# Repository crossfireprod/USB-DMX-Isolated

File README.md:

Fully Isolated USB DMX Adapter
==================

This USB DMX adapter is designed to be an functional foray into PCB design and assembly using primarily surface mount components.  The use of an isolating RS-485 transceiver differentiates this USB DMX adapter from others that can be purchased or built at a similar price point.

Bill Of Materials
-------------------

A Bill Of Materials detailing the specific parts used in my most recent production run can be found on [Octopart](https://octopart.com/bom-tool/TxEq1b9y).  Pricing is more or less optimized around single unit quanties.

Repository Contents
-------------------

* **/Hardware** - Eagle Schematic & PCB Layout
* **/Images** - Images of the schematic / PCB design, as well as fully assembled USB DMX adapters.

License
-------------------

All contents of this repository are released under [Creative Commons Share-alike 4.0](http://creativecommons.org/licenses/by-sa/4.0/).

NOTE:  While every effort was made to follow the necessary design rules to maintain proper isolation between the USB and RS-485 interfaces, this design is a hobby project and as such should *not* be relied upon to protect life, limb, your equipment, etc.

Design By: [*ZachCross.com*](https://ZachCross.com)

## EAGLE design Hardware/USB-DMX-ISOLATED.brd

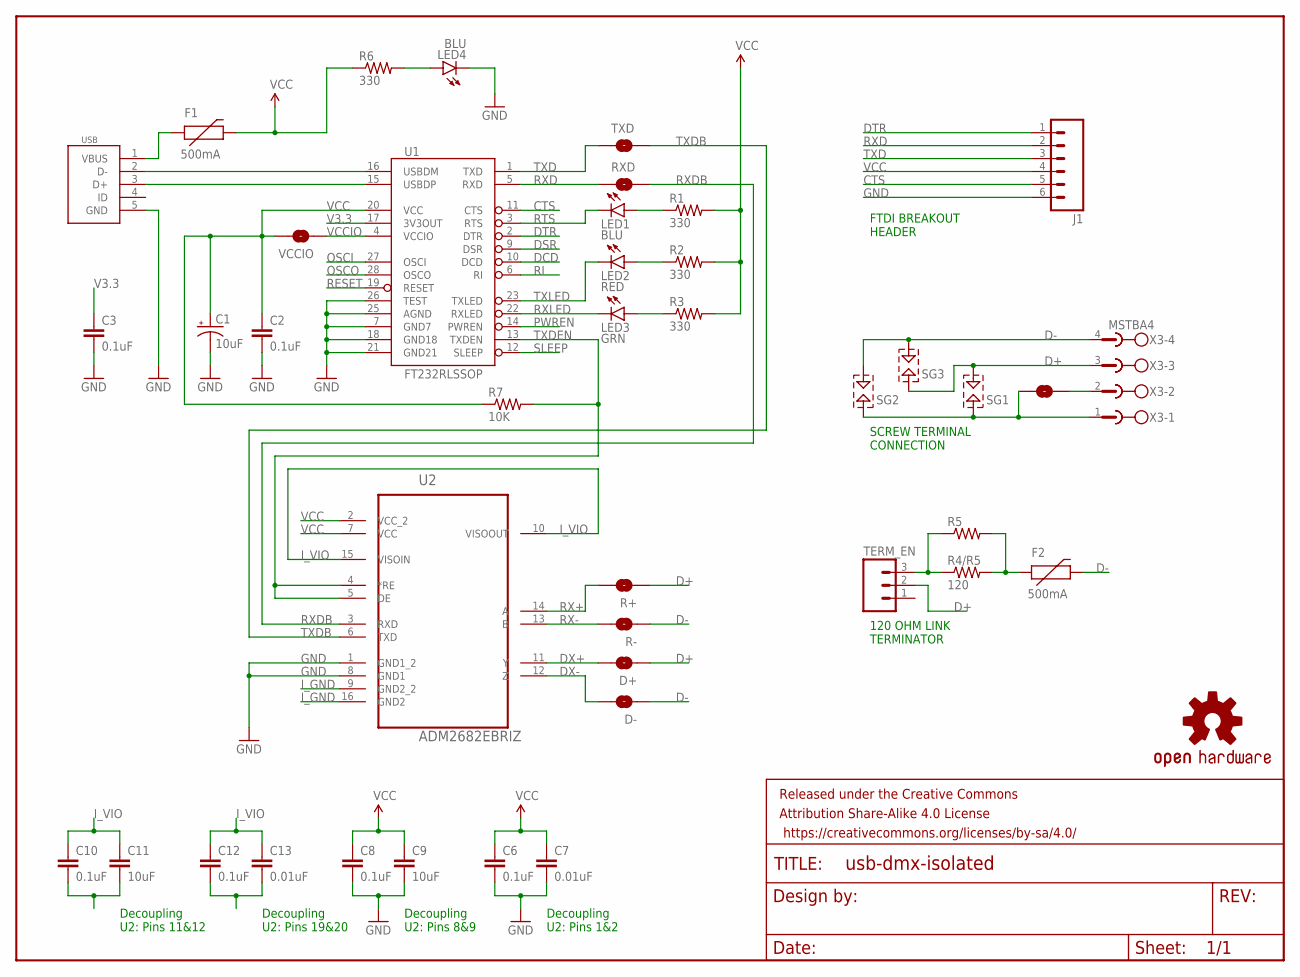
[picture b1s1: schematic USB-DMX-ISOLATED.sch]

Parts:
C1: 10uF; EIA3216
C2, C3, C6, C8, C10, C12: 0.1uF; 1206
C7, C13: 0.01uF; 1206
C9, C11: 10uF; 1206
D+: SOLDERJUMPERTRACE; SJ_2S-TRACE
D-: SOLDERJUMPERTRACE; SJ_2S-TRACE
F1, F2: 500mA; PTC-1206
FRAME1: FRAME-LETTERNO_PACKAGE; DUMMY
J1: M06LOCK; 1X06_LOCK
LED1, LED4: BLU; LED-1206
LED2: RED; LED-1206
LED3: GRN; LED-1206
LOGO1: OSHW-LOGOS; OSHW-LOGO-S
P2_COM: SOLDERJUMPERTRACE; SJ_2S-TRACE
R1, R2, R3, R6: 330; 1206
R4/R5: 120; 1206
R5: RESISTORPTH-1W; AXIAL-0.6
R7: 10K; 1206
R+: SOLDERJUMPERTRACE; SJ_2S-TRACE
R-: SOLDERJUMPERTRACE; SJ_2S-TRACE
RXD: SOLDERJUMPERTRACE; SJ_2S-TRACE
SG1, SG2, SG3: SPARK-GAP-8
TERM_EN: M03LOCK; 1X03_LOCK
TXD: SOLDERJUMPERTRACE; SJ_2S-TRACE
U1: FT232RLSSOP; SSOP28DB
U2: ADM2682EBRIZ; SOIC127P1032X265-16N
USB: USB-CON-5PIN-105017-0001; USB-MICRO-MOLEX-105017-0001
VCCIO: SOLDERJUMPERTRACE; SJ_2S-TRACE
X3: MSTBA4

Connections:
CTS: J1.5, U1.11 (CTS)
D+: D+.1, R+.1, SG1.1, SG3.2, TERM_EN.2, X3.3
D-: D-.1, F2.2, R-.1, SG2.1, SG3.1, X3.4
DCD: U1.10 (DCD)
DSR: U1.9 (DSR)
DTR: J1.1, U1.2 (DTR)
DX+: D+.2, U2.11 (Y)
DX-: D-.2, U2.12 (Z)
GND: C1.C (-), C2.2, C3.2, C6.2, C7.2, C8.2, C9.2, J1.6, LED4.C, U1.7 (GND7), U1.18 (GND18), U1.21 (GND21), U1.25 (AGND), U1.26 (TEST), U2.1 (GND1_2), U2.8 (GND1), USB.5 (GND)
I_GND: C10.2, C11.2, C12.2, C13.2, P2_COM.1, SG1.2, SG2.2, U2.9 (GND2_2), U2.16 (GND2), X3.1
I_VIO: C10.1, C11.1, C12.1, C13.1, U2.10 (VISOOUT), U2.15 (VISOIN)
unnamed: LED4.A, R6.2
unnamed: P2_COM.2, X3.2
unnamed: R4/R5.1, R5.P$1 (1), TERM_EN.3
unnamed: F2.1, R4/R5.2, R5.P$2 (2)
unnamed: LED3.A, R3.1
unnamed: LED1.A, R1.1
unnamed: LED2.A, R2.1
OSCI: U1.27 (OSCI)
OSCO: U1.28 (OSCO)
PWREN: U1.14 (PWREN)
RESET: U1.19 (RESET)
RI: U1.6 (RI)
RTS: LED1.C, U1.3 (RTS)
RX+: R+.2, U2.14 (A)
RX-: R-.2, U2.13 (B)
RXD: J1.2, RXD.1, U1.5 (RXD)
RXDB: RXD.2, U2.3 (RXD)
RXLED: LED3.C, U1.22 (RXLED)
SLEEP: U1.12 (SLEEP)
TXD: J1.3, TXD.1, U1.1 (TXD)
TXDB: TXD.2, U2.6 (TXD)
TXDEN: R7.2, U1.13 (TXDEN), U2.4 (*RE), U2.5 (DE)
TXLED: LED2.C, U1.23 (TXLED)
USB_D+: U1.15 (USBDP), USB.3 (D+)
USB_D-: U1.16 (USBDM), USB.2 (D-)
V3.3: C3.1, U1.17 (3V3OUT)
VBUS: F1.1, USB.1 (VBUS)
VCC: C1.A (+), C2.1, C6.1, C7.1, C8.1, C9.1, F1.2, J1.4, R1.2, R2.2, R3.2, R6.1, R7.1, U1.20 (VCC), U2.2 (VCC_2), U2.7 (VCC), VCCIO.2
VCCIO: U1.4 (VCCIO), VCCIO.1

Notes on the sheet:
Decoupling U2: Pins 1&2
Decoupling U2: Pins 8&9
Decoupling U2: Pins 11&12
Decoupling U2: Pins 19&20
120 OHM LINK TERMINATOR
SCREW TERMINAL CONNECTION
FTDI BREAKOUT HEADER

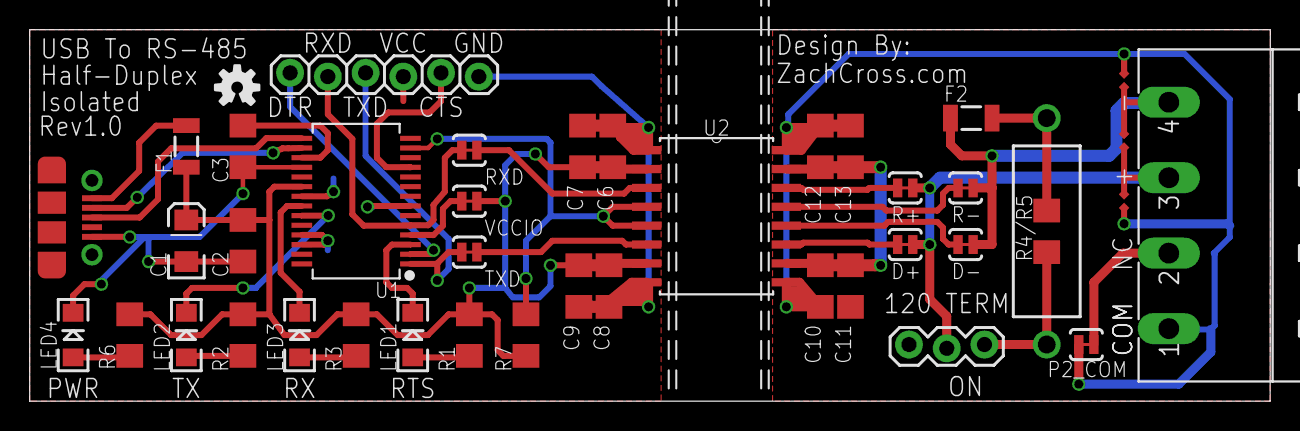
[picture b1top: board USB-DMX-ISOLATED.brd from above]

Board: 2 copper layers, 83.5 x 25.0 mm, 43 parts (0 on the bottom side), 32 nets.

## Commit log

2017-02-03 Added base design files & images.
2017-02-03 Added safety disclaimer to README.

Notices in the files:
parts and their libraries:
SparkFun-PowerIC: Licensing: Creative Commons ShareAlike 4.0 International - https://creativecommons.org/licenses/by-sa/4.0
supressor: Copyright (C) 2009, Bob Starr
SparkFun-Aesthetics: Released under the Creative Commons Attribution Share-Alike 4.0 License
